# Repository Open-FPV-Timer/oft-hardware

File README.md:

# oft-hardware: carrier boards for the Open FPV Timer

KiCad 9 drafts of the boards that replace the jumper wires in the reference builds
([oft-spec §9](../oft-spec/oft-spec.md)). One design in four sizes. All are first drafts made
before any hardware has been measured or powered, so treat every dimension as provisional.

| Board | Nodes | Shape | Size | Layers |
|---|---|---|---|---|
| [carrier-1](carrier-1/) | 1 | stick | 96 x 25 mm | 2 |
| [carrier-2](carrier-2/) | 2 | one row above the Timer | 66 x 53 mm | 2 |
| [carrier-4](carrier-4/) | 4 | a row of two above and below | 66 x 80 mm | 2 |
| [carrier-8](carrier-8/) | 8 | a row of four above and below | 94 x 80 mm | 2 |

Every board carries one Waveshare RP2350-POE-ETH Timer and Seeed XIAO ESP32-C5 Nodes. Slots can
be left empty.

- **1 Node** is a 25 mm stick for the gate's top bar: Ethernet in at one end, the Node at the
  other.
- **2, 4 and 8 Nodes** put the Timer across the middle of the board, RJ45 at the left edge,
  with the XIAOs in rows either side of it. USB-C ports face the outer edges so every one
  stays reachable; antenna connectors face the Timer.

## Why these parts

- **RP2350-POE-ETH** is MCU, Ethernet and PoE on one $25 module. Replacing it means designing a
  PoE front end, which is not worth it for a draft.
- **XIAO ESP32-C5** brings its own regulator, USB-C for flashing and a finished RF section.
  A bare ESP32-C5 module would save roughly $9 a Node but needs a 3.3 V supply, boot and USB
  circuitry and reflow assembly. That is the natural second revision of the 4 and 8-Node
  boards once this one is proven, where hand-soldering eight XIAOs also stops being fun.

## Pin map

Slots are numbered left to right, top row first. The pins follow the layout: each row's UART
pads are wired to the Timer pin row facing it, in the same left-to-right order, so nothing
crosses. UART1 (GP4/GP5) is the pair `oft-timer-rp2350/src/board.rs` gives Node 1 by default; the
other slots' pins are set on the Timer's Advanced page.

| Board | Slot: Timer TX / RX (to Node D7 / from Node D6) |
|---|---|
| carrier-1 | 1: GP4/GP5 (UART1) |
| carrier-2 | 1: GP4/GP5 (UART1), 2: GP0/GP1 (UART0) |
| carrier-4 | 1: GP4/GP5 (UART1), 2: GP0/GP1 (UART0), 3: GP13/GP15, 4: GP22/GP28 |
| carrier-8 | 1: GP10/GP11, **2: GP4/GP5 (UART1)**, 3: GP2/GP3, **4: GP0/GP1 (UART0)**, 5: GP12/GP13, 6: GP14/GP15, 7: GP22/GP26, 8: GP27/GP28 |

Note the 8-Node board: the UART1 slot is slot 2, not slot 1. Slots without a hardware UART
need PIO UARTs; six of them is every PIO state machine the RP2350 has. Shared by every slot:
SYNC on GP6, to each XIAO's D8. EN and BOOT are not wired: the Timer restarts a Node and
reaches its bootloader over the Node's own UART. The map is in `gen/carrier.py`.

## Circuit

- **Data lines:** 220R in series on every UART line and on SYNC, to limit the current when one
  board is powered and the other is not.
- **No EN or BOOT lines.** The Timer restarts a Node, and sends it to its bootloader for a
  firmware update, with messages on that Node's UART. A Node whose firmware stops answering
  is recovered with its own buttons (hold BOOT, tap RESET) or its USB-C port, both of which
  stay reachable at the board edge.
- **Power:** each XIAO runs from the Timer's Vsys through its own Schottky diode (B5819W) with a
  10 uF capacitor. A laptop on one XIAO's USB-C then powers only that XIAO and cannot back-feed
  the Timer. The diode costs about 0.3 to 0.4 V, so the XIAO sees roughly 4.3 V.

## How the modules mount

- **RP2350-POE-ETH** plugs into two 1x16 female sockets, component side up. The link resistors
  sit on the carrier under it or just beside its pin rows.
- **XIAO ESP32-C5** is soldered flat by its castellated edge pads, and by nothing else: no
  pad on its underside is used. SYNC is on D8 (GPIO8), the `oft-node-c5` default. The first
  draft soldered EN, MTMS (GPIO2, then the SYNC input) and BOOT through plated holes from the
  back of the carrier; those holes are gone.

Fab-assembled: resistors, capacitors, diodes, all top side. Hand-soldered: the two sockets and
the XIAOs.

## Files

- `b1-proto-30x70/`: the hand-built one-Node Timer on a 30 x 70 mm protoboard, Timer on top
  and Node underneath: where each pin goes, the five wires, and its printable case with
  slide-on flat, pipe and strap bases. No fab needed. This is the one-Node build to make.
- `carrier-N/`: the KiCad project for each size.
- `lib/`: shared symbols (`oft.kicad_sym`) and footprints (`oft.pretty`) for the two modules.
  The Timer footprint is drawn from Waveshare's dimension drawing; the XIAO pad positions come
  from Seeed's own `XIAO-ESP32-C5-SMD` footprint (MIT, github.com/Seeed-Studio/OSHW-XIAO-Series;
  its notice is in `NOTICE.md`).
- `gen/`: the scripts that produced the drafts. `carrier_sch.py` draws the schematic for any
  size. `stick_pcb.py` lays out the 1-Node board and `grid_pcb.py` the 2, 4 and 8-Node boards;
  placement and routing are written out by hand, and each file's header explains its routing
  plan. `parts.py` writes the footprints; `sch.py` and `pcb.py` are helpers. Regenerating overwrites a board, so stop regenerating a size once you start editing
  it in KiCad.
- `tools/kicad.sh`: runs anything inside the official `kicad/kicad:9.0` container. Nothing is
  installed on the host.

## Regenerate and check

```
tools/kicad.sh gen/build.sh 4          # 4-Node board: regenerate, ERC, DRC, previews
tools/kicad.sh gen/build.sh 4 check    # ERC, DRC, previews only
```

Outputs land in `carrier-N/out/` (gitignored): `schematic.pdf`, `render-top.png`,
`render-bottom.png`, `layout-top.svg`, `layout-bottom.svg`, `erc.rpt`, `drc.rpt`.

After opening a board in the KiCad GUI, press B once to refill zones.

## Check before ordering

1. **Timer pin grid.** Two rows of 16 on a 2.54 mm pitch, 17.78 mm apart, first pin 1.35 mm
   from the USB-C end. Taken from Waveshare's drawing, not measured. Put calipers on a real
   board. The numbers are at the top of `gen/parts.py`.
2. **Timer pin order.** Pin 1 (GP0) is at the USB-C end of one row and pin 32 (VBUS) at the
   USB-C end of the other. Waveshare's pinout drawing shows the label side; the footprint
   mirrors it for the component side. Check the pins in the table above against the silkscreen.
3. **XIAO underside clearance.** The carrier has no top copper under the XIAO body, so its
   underside pads (EN, BOOT, 3V3, GND, JTAG, BAT, thermal) touch only solder mask. Confirm
   nothing on the XIAO's underside stands proud.
4. **Flashing without EN and BOOT.** Run on a breadboard 2026-11-27, four Nodes, many
   writes, on hardware UART and PIO links. A Node whose write is interrupted by a power
   cut still needs its BOOT and RESET buttons or its USB port, so keep both reachable in
   the case until the Node has two firmware slots.
5. **SYNC vias.** Each D8 pad has a 0.6 mm via 2.6 mm outside it, in the parts column. Check
   it clears your soldering of the edge pads.
6. **Power for 4 and 8 Nodes.** Everything draws through the Timer module's Vsys pin. The Node
   current while sampling and the PoE module's 5 V rating are both still unmeasured (HBOM).
   Eight Nodes will very likely need a separate 5 V input on the carrier, which this draft does
   not have.
7. **Firmware.** The Timer firmware drives up to four Nodes (its `multi-node` work): slot
   pins are a setting, Node 1 on UART1, Node 2 on UART0, Nodes 3 and 4 on PIO UARTs, which
   have not yet run on hardware. The carrier-1, -2 and -4 pin maps above fit that. The
   8-Node board needs four more PIO links than the firmware has.
8. **VSYS on the 2 and 4-Node boards** squeezes between two Timer pins as a 0.4 mm track for a
   few millimetres. Fine for two Nodes; check it against the measured current for four.
9. **Antenna end clearance.** On the 2, 4 and 8-Node boards the XIAOs' antenna ends sit 8 mm
   from the Timer's pin rows, and the module overhangs its pins by 1.6 mm, 11 mm up. Check a
   u.FL plug and its cable fit beside the Timer and its PoE module.
10. **Antennas.** The spec leans towards one gate antenna and a splitter for multi-Node
    builds; that is off these boards.
11. **Socket height.** On the stick, a USB-C plug in the Timer module passes over the XIAO.
    That needs standard 8.5 mm sockets; low-profile sockets will not clear.
12. **LCSC part numbers** in the schematic `LCSC` fields were filled in from memory. Confirm
    each one before generating a JLCPCB BOM.
13. **Mounting.** M2.5 holes, positions arbitrary: four at the corners of the stick, three or
    four beside and under the Timer on the others (those under the module are only reachable
    with it unplugged). Decide alongside the case, along with where the foil wall goes.

## Acknowledgements

OFT is inspired by [FPVGate](https://github.com/LouisHitchcock/FPVGateC5MK), which showed
that an ESP32-C5 can time laps, and builds on [widscan58](https://github.com/CapnBry/widscan58),
esp-sdr, C5VRX and RotorHazard. The full list is in the
[oft README](https://github.com/Open-FPV-Timer/oft#acknowledgements).

## Licence

GPL-3.0-or-later, the same as the other OFT repos. See [LICENSE](LICENSE).

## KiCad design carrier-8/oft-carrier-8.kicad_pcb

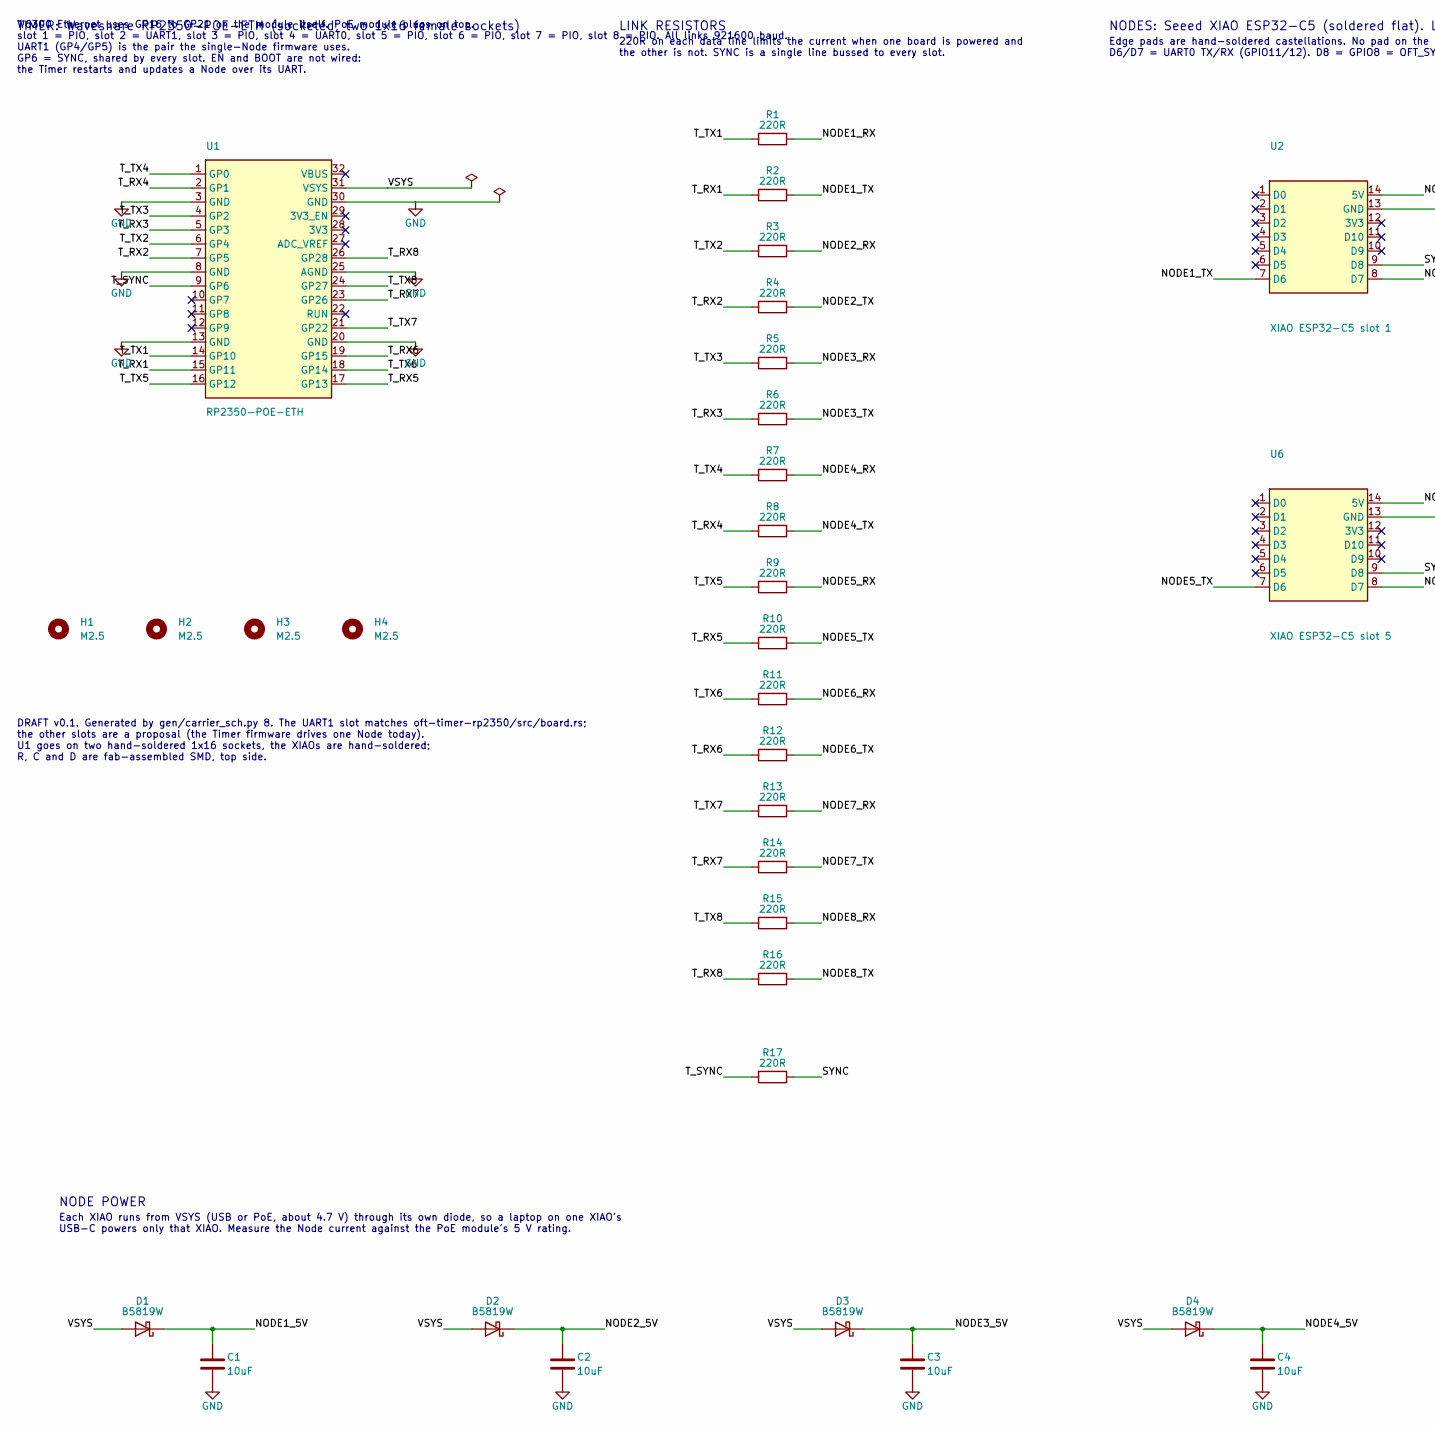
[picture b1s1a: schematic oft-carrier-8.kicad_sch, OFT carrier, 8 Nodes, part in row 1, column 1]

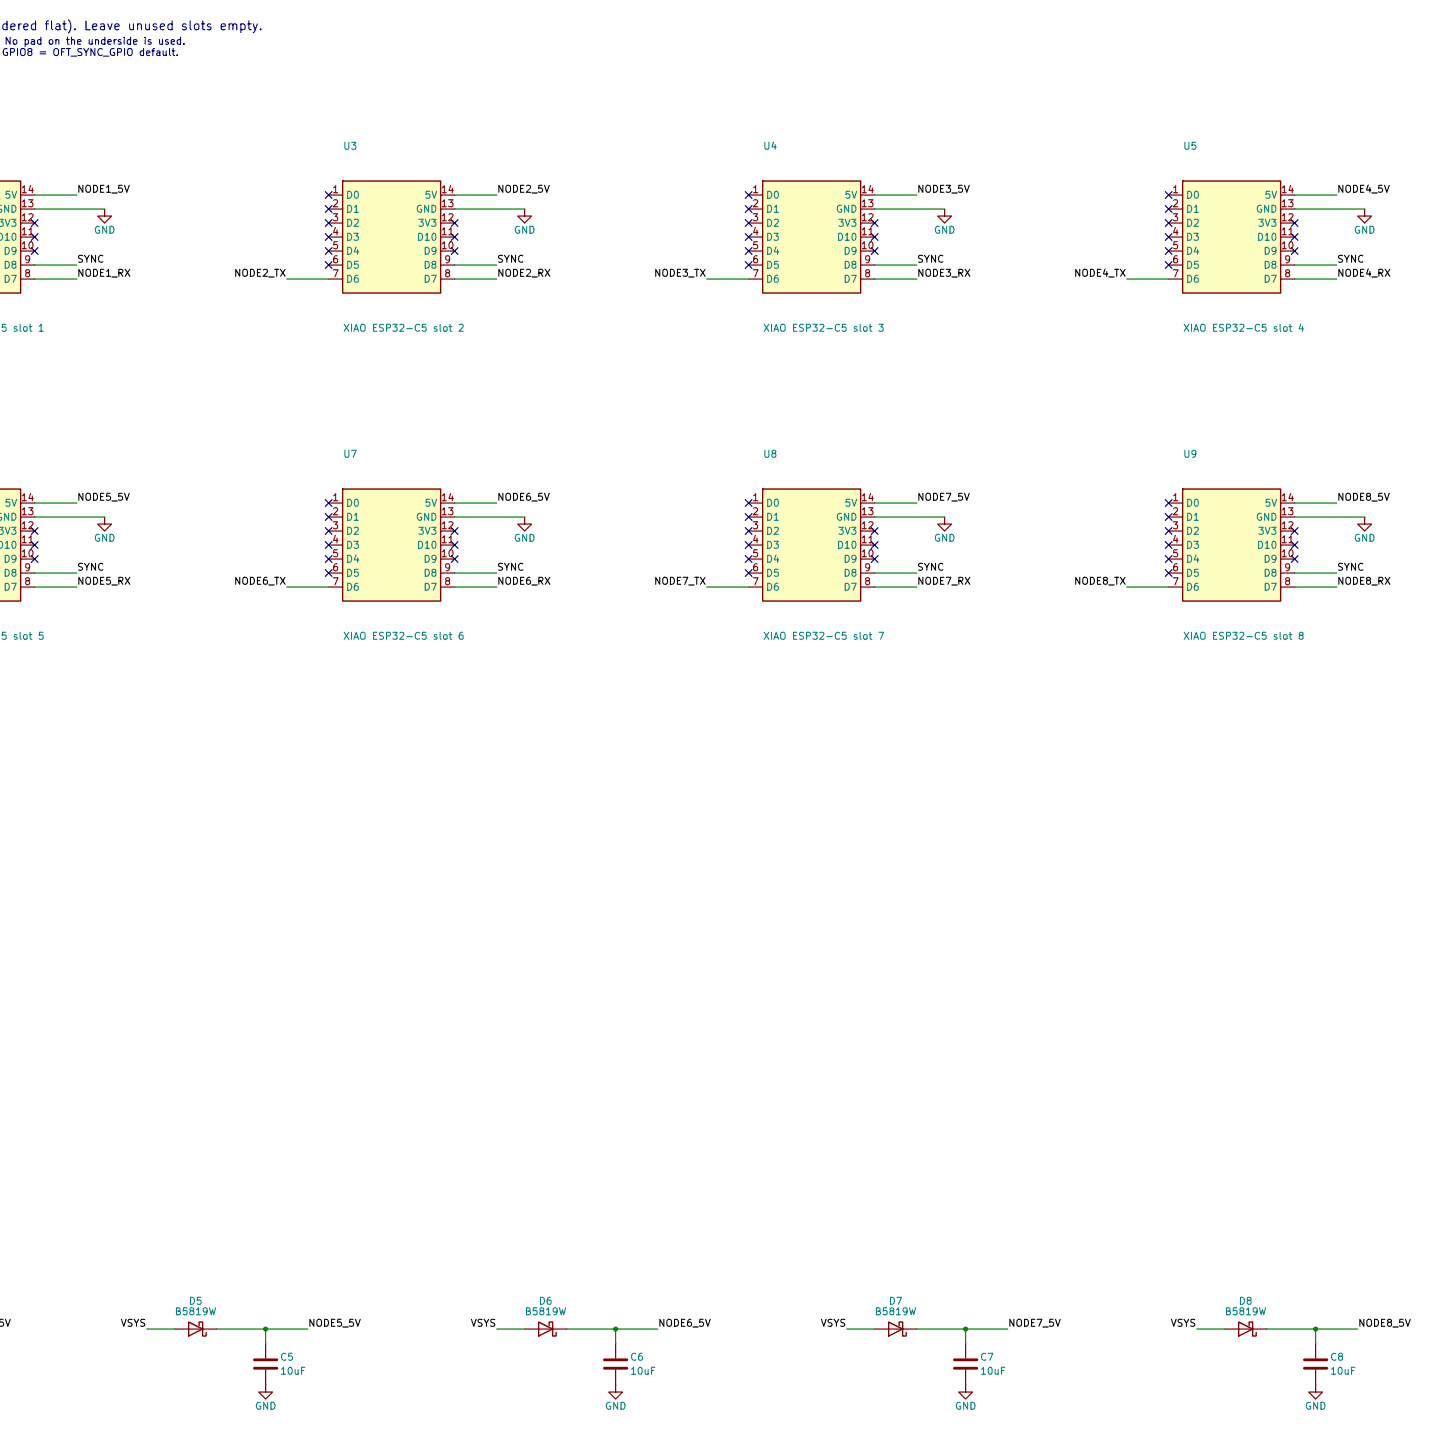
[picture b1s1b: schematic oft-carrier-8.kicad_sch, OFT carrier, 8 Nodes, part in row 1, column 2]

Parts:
C1, C2, C3, C4, C5, C6, C7, C8: 10uF; C_0805_2012Metric; LCSC C15850
D1, D2, D3, D4, D5, D6, D7, D8: B5819W; D_SOD-123; MPN B5819W; LCSC C8598
H1, H2, H3, H4: M2.5; MountingHole_2.7mm_M2.5
R1, R2, R3, R4, R5, R6, R7, R8, R9, R10, R11, R12, R13, R14, R15, R16, R17: 220R; R_0603_1608Metric; LCSC C22962
U1: RP2350-POE-ETH; RP2350-POE-ETH_Socket; MPN Waveshare RP2350-POE-ETH
U2: XIAO ESP32-C5 slot 1; XIAO-ESP32-C5_SMD; MPN Seeed 100010048
U3: XIAO ESP32-C5 slot 2; XIAO-ESP32-C5_SMD; MPN Seeed 100010048
U4: XIAO ESP32-C5 slot 3; XIAO-ESP32-C5_SMD; MPN Seeed 100010048
U5: XIAO ESP32-C5 slot 4; XIAO-ESP32-C5_SMD; MPN Seeed 100010048
U6: XIAO ESP32-C5 slot 5; XIAO-ESP32-C5_SMD; MPN Seeed 100010048
U7: XIAO ESP32-C5 slot 6; XIAO-ESP32-C5_SMD; MPN Seeed 100010048
U8: XIAO ESP32-C5 slot 7; XIAO-ESP32-C5_SMD; MPN Seeed 100010048
U9: XIAO ESP32-C5 slot 8; XIAO-ESP32-C5_SMD; MPN Seeed 100010048

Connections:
/NODE1_5V: C1.1, D1.1 (K), U2.14 (5V)
/NODE1_RX: R1.2, U2.8 (D7)
/NODE1_TX: R2.2, U2.7 (D6)
/NODE2_5V: C2.1, D2.1 (K), U3.14 (5V)
/NODE2_RX: R3.2, U3.8 (D7)
/NODE2_TX: R4.2, U3.7 (D6)
/NODE3_5V: C3.1, D3.1 (K), U4.14 (5V)
/NODE3_RX: R5.2, U4.8 (D7)
/NODE3_TX: R6.2, U4.7 (D6)
/NODE4_5V: C4.1, D4.1 (K), U5.14 (5V)
/NODE4_RX: R7.2, U5.8 (D7)
/NODE4_TX: R8.2, U5.7 (D6)
/NODE5_5V: C5.1, D5.1 (K), U6.14 (5V)
/NODE5_RX: R9.2, U6.8 (D7)
/NODE5_TX: R10.2, U6.7 (D6)
/NODE6_5V: C6.1, D6.1 (K), U7.14 (5V)
/NODE6_RX: R11.2, U7.8 (D7)
/NODE6_TX: R12.2, U7.7 (D6)
/NODE7_5V: C7.1, D7.1 (K), U8.14 (5V)
/NODE7_RX: R13.2, U8.8 (D7)
/NODE7_TX: R14.2, U8.7 (D6)
/NODE8_5V: C8.1, D8.1 (K), U9.14 (5V)
/NODE8_RX: R15.2, U9.8 (D7)
/NODE8_TX: R16.2, U9.7 (D6)
/SYNC: R17.2, U2.9 (D8), U3.9 (D8), U4.9 (D8), U5.9 (D8), U6.9 (D8), U7.9 (D8), U8.9 (D8), U9.9 (D8)
/T_RX1: R2.1, U1.15 (GP11)
/T_RX2: R4.1, U1.7 (GP5)
/T_RX3: R6.1, U1.5 (GP3)
/T_RX4: R8.1, U1.2 (GP1)
/T_RX5: R10.1, U1.17 (GP13)
/T_RX6: R12.1, U1.19 (GP15)
/T_RX7: R14.1, U1.23 (GP26)
/T_RX8: R16.1, U1.26 (GP28)
/T_SYNC: R17.1, U1.9 (GP6)
/T_TX1: R1.1, U1.14 (GP10)
/T_TX2: R3.1, U1.6 (GP4)
/T_TX3: R5.1, U1.4 (GP2)
/T_TX4: R7.1, U1.1 (GP0)
/T_TX5: R9.1, U1.16 (GP12)
/T_TX6: R11.1, U1.18 (GP14)
/T_TX7: R13.1, U1.21 (GP22)
/T_TX8: R15.1, U1.24 (GP27)
/VSYS: D1.2 (A), D2.2 (A), D3.2 (A), D4.2 (A), D5.2 (A), D6.2 (A), D7.2 (A), D8.2 (A), U1.31 (VSYS)
GND: C1.2, C2.2, C3.2, C4.2, C5.2, C6.2, C7.2, C8.2, U1.3 (GND), U1.8 (GND), U1.13 (GND), U1.20 (GND), U1.25 (AGND), U1.30 (GND), U2.13 (GND), U3.13 (GND), U4.13 (GND), U5.13 (GND), U6.13 (GND), U7.13 (GND), U8.13 (GND), U9.13 (GND)

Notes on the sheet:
TIMER: Waveshare RP2350-POE-ETH (socketed, two 1x16 female sockets)
W6300 Ethernet uses GP16 to GP21 on the module itself. PoE module plugs on top. slot 1 = PIO, slot 2 = UART1, slot 3 = PIO, slot 4 = UART0, slot 5 = PIO, slot 6 = PIO, slot 7 = PIO, slot 8 = PIO. All links 921600 baud. UART1 (GP4/GP5) is the pair the single-Node firmware uses. GP6 = SYNC, shared by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
LINK RESISTORS
220R on each data line limits the current when one board is powered and the other is not. SYNC is a single line bussed to every slot.
NODES: Seeed XIAO ESP32-C5 (soldered flat). Leave unused slots empty.
Edge pads are hand-soldered castellations. No pad on the underside is used. D6/D7 = UART0 TX/RX (GPIO11/12). D8 = GPIO8 = OFT_SYNC_GPIO default.
NODE POWER
Each XIAO runs from VSYS (USB or PoE, about 4.7 V) through its own diode, so a laptop on one XIAO's USB-C powers only that XIAO. Measure the Node current against the PoE module's 5 V rating.
DRAFT v0.1. Generated by gen/carrier_sch.py 8. The UART1 slot matches oft-timer-rp2350/src/board.rs; the other slots are a proposal (the Timer firmware drives one Node today). U1 goes on two hand-soldered 1x16 sockets, the XIAOs are hand-soldered; R, C and D are fab-assembled SMD, top side.

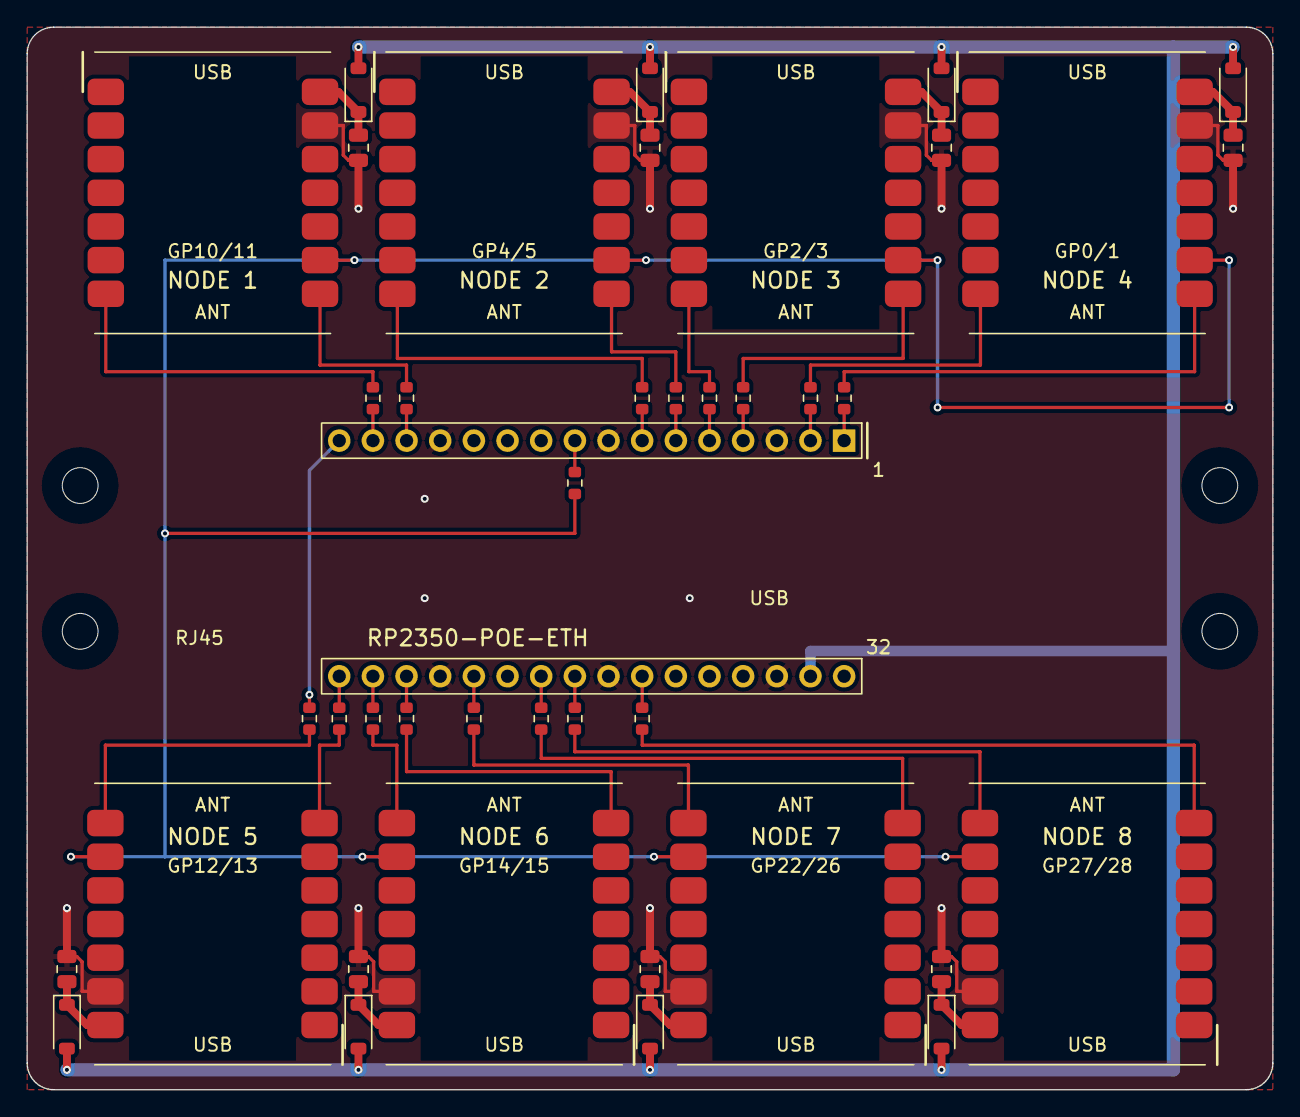
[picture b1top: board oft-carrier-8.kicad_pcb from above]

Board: 2 copper layers, 94.0 x 80.2 mm, 46 parts (0 on the bottom side), 44 nets.

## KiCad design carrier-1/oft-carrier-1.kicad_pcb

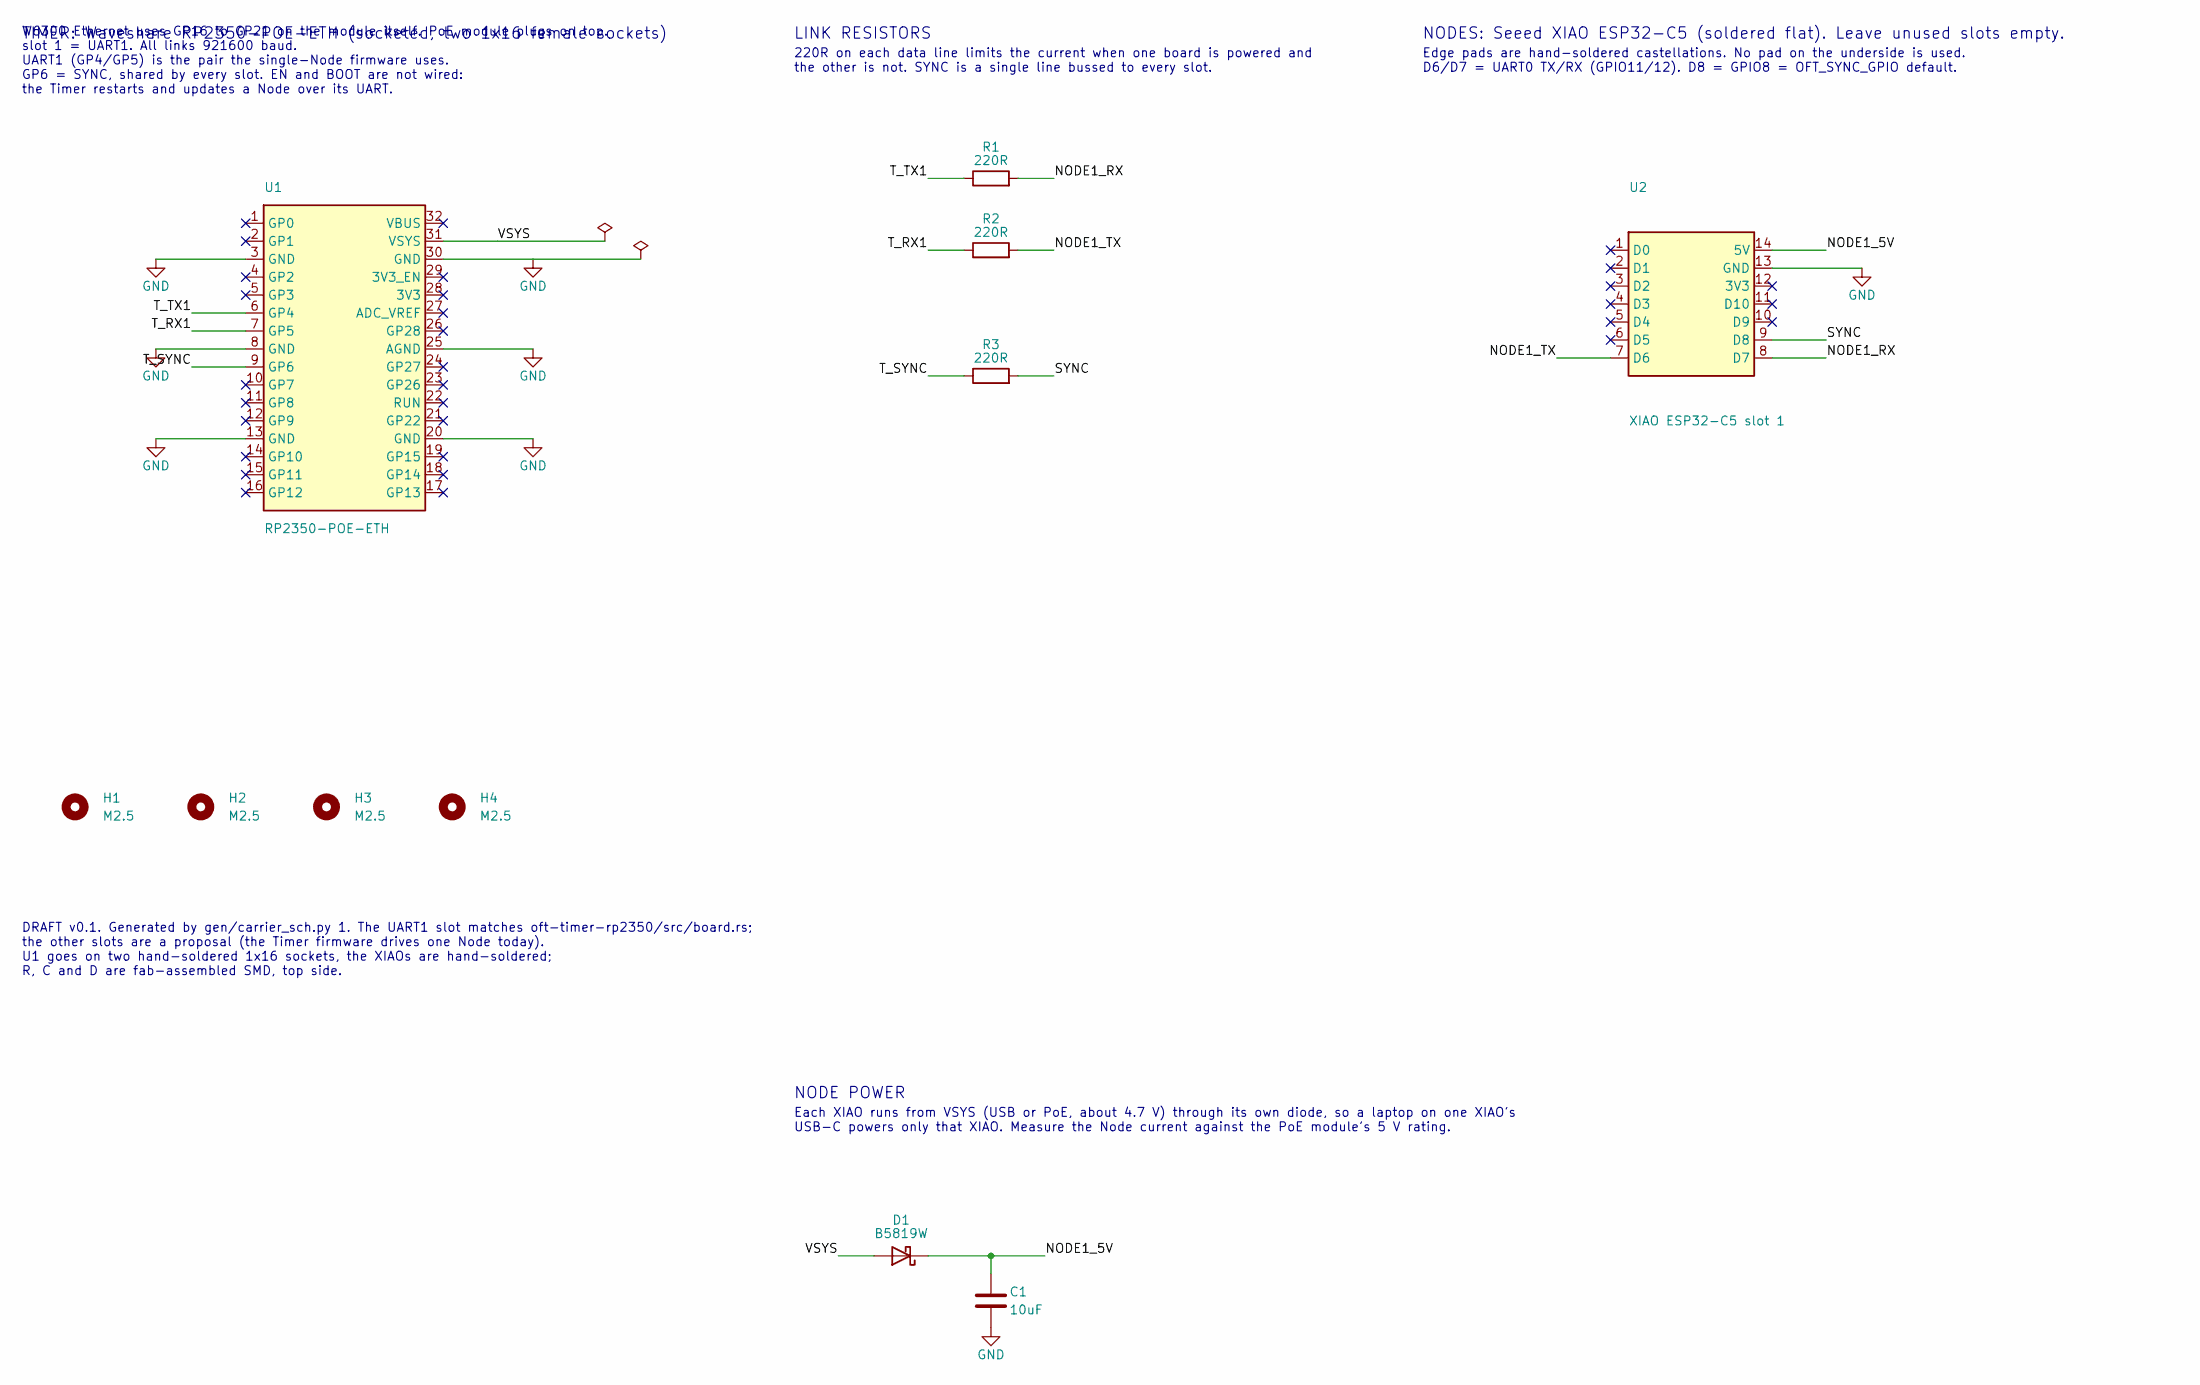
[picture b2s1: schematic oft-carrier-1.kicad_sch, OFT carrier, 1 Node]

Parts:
C1: 10uF; C_0805_2012Metric; LCSC C15850
D1: B5819W; D_SOD-123; MPN B5819W; LCSC C8598
H1, H2, H3, H4: M2.5; MountingHole_2.7mm_M2.5
R1, R2, R3: 220R; R_0603_1608Metric; LCSC C22962
U1: RP2350-POE-ETH; RP2350-POE-ETH_Socket; MPN Waveshare RP2350-POE-ETH
U2: XIAO ESP32-C5 slot 1; XIAO-ESP32-C5_SMD; MPN Seeed 100010048

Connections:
/NODE1_5V: C1.1, D1.1 (K), U2.14 (5V)
/NODE1_RX: R1.2, U2.8 (D7)
/NODE1_TX: R2.2, U2.7 (D6)
/SYNC: R3.2, U2.9 (D8)
/T_RX1: R2.1, U1.7 (GP5)
/T_SYNC: R3.1, U1.9 (GP6)
/T_TX1: R1.1, U1.6 (GP4)
/VSYS: D1.2 (A), U1.31 (VSYS)
GND: C1.2, U1.3 (GND), U1.8 (GND), U1.13 (GND), U1.20 (GND), U1.25 (AGND), U1.30 (GND), U2.13 (GND)

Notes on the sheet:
TIMER: Waveshare RP2350-POE-ETH (socketed, two 1x16 female sockets)
W6300 Ethernet uses GP16 to GP21 on the module itself. PoE module plugs on top. slot 1 = UART1. All links 921600 baud. UART1 (GP4/GP5) is the pair the single-Node firmware uses. GP6 = SYNC, shared by every slot. EN and BOOT are not wired: the Timer restarts and updates a Node over its UART.
LINK RESISTORS
220R on each data line limits the current when one board is powered and the other is not. SYNC is a single line bussed to every slot.
NODES: Seeed XIAO ESP32-C5 (soldered flat). Leave unused slots empty.
Edge pads are hand-soldered castellations. No pad on the underside is used. D6/D7 = UART0 TX/RX (GPIO11/12). D8 = GPIO8 = OFT_SYNC_GPIO default.
NODE POWER
Each XIAO runs from VSYS (USB or PoE, about 4.7 V) through its own diode, so a laptop on one XIAO's USB-C powers only that XIAO. Measure the Node current against the PoE module's 5 V rating.
DRAFT v0.1. Generated by gen/carrier_sch.py 1. The UART1 slot matches oft-timer-rp2350/src/board.rs; the other slots are a proposal (the Timer firmware drives one Node today). U1 goes on two hand-soldered 1x16 sockets, the XIAOs are hand-soldered; R, C and D are fab-assembled SMD, top side.

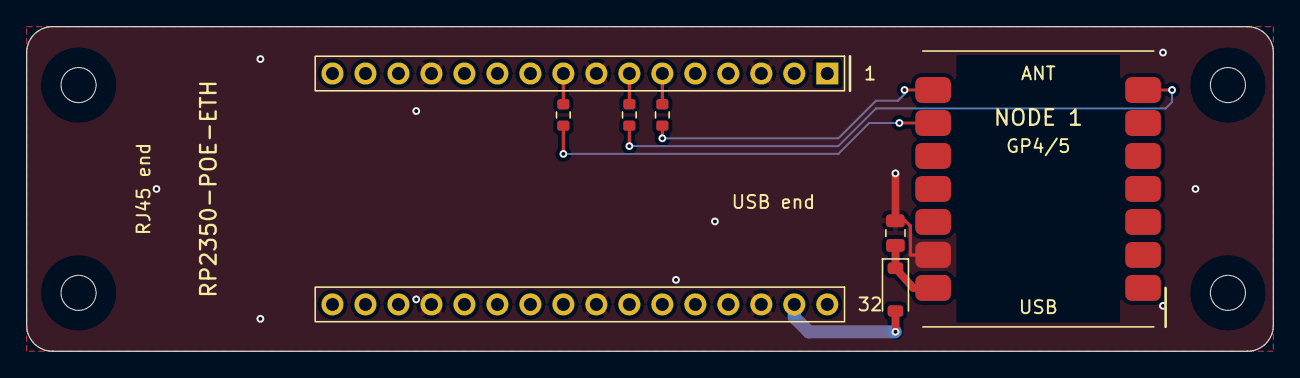
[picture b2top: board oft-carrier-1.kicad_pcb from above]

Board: 2 copper layers, 96.0 x 25.0 mm, 11 parts (0 on the bottom side), 9 nets.
